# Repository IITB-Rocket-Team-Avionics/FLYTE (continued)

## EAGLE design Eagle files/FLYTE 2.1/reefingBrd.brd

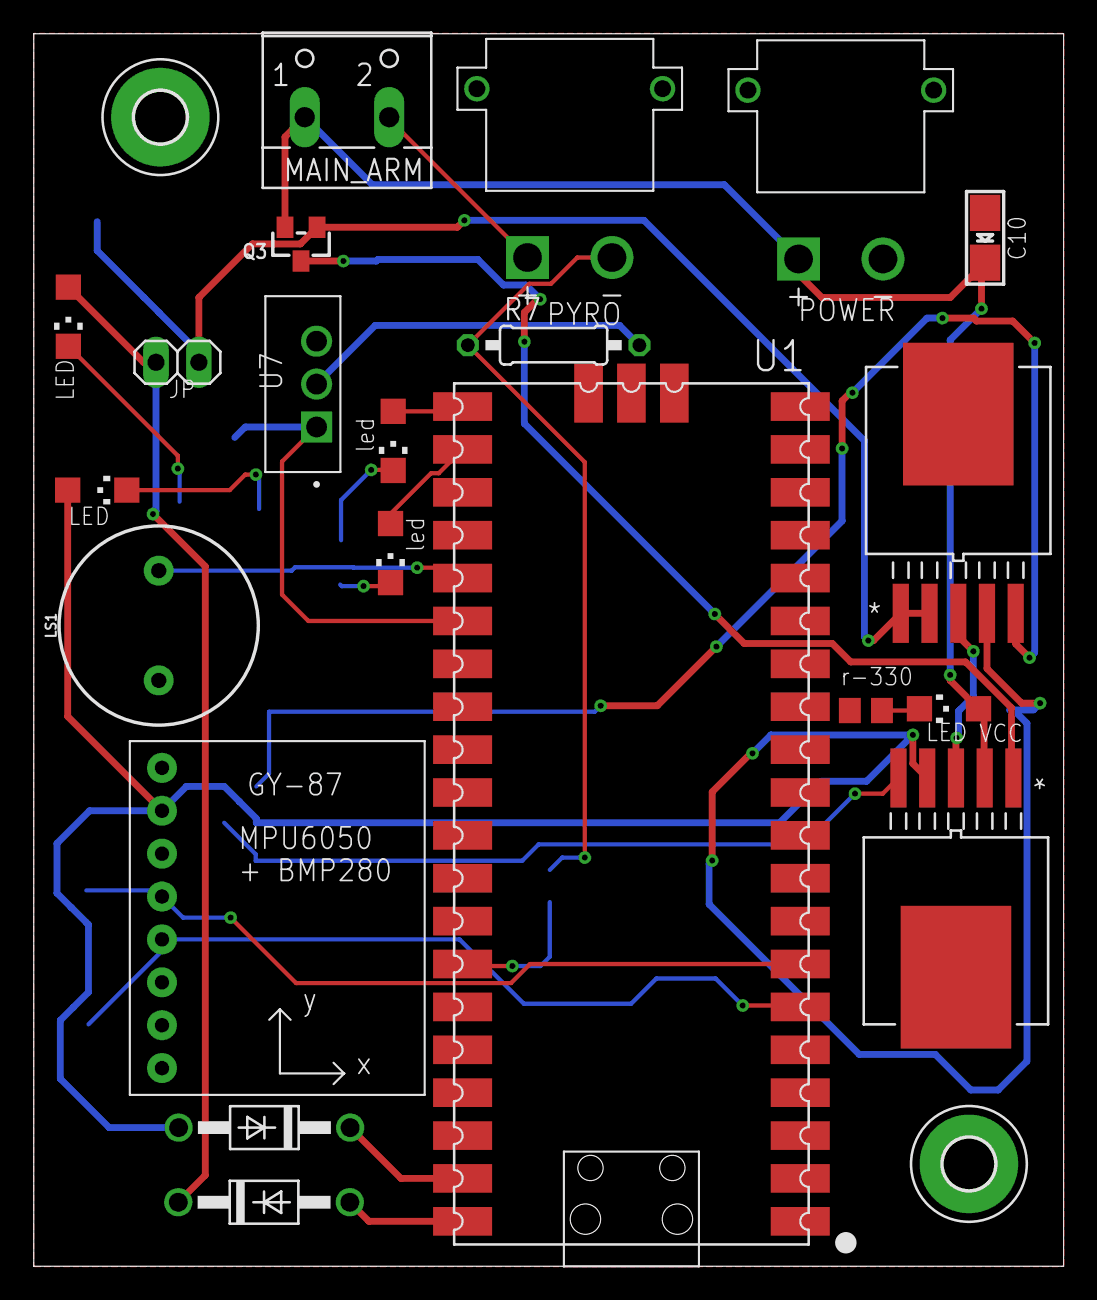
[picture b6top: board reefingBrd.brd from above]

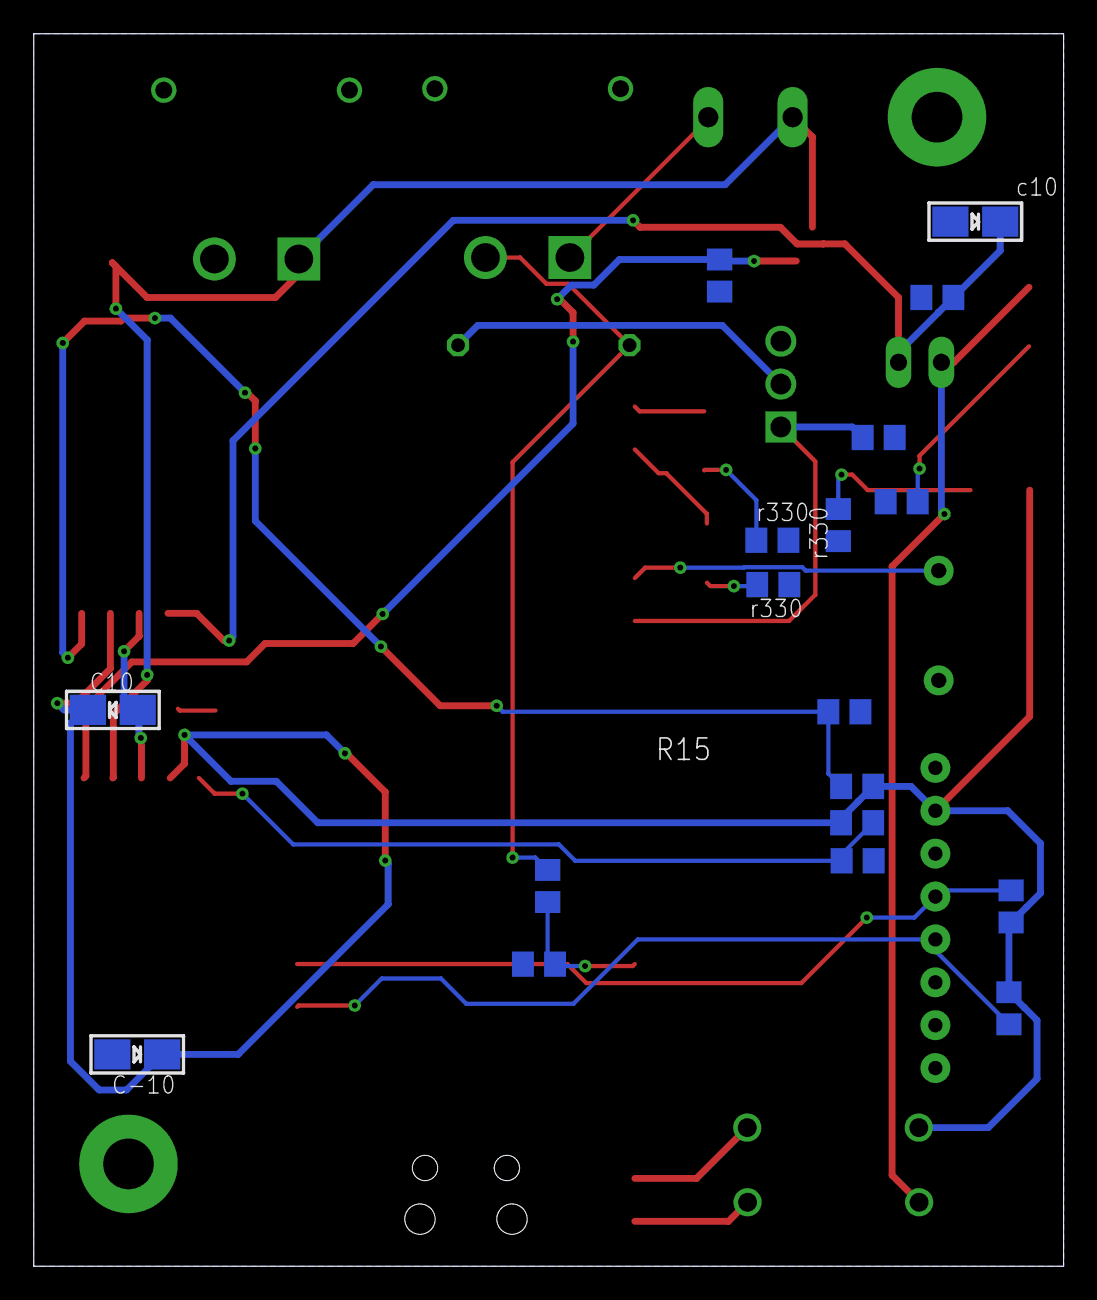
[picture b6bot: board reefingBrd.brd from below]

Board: 2 copper layers, 61.0 x 73.0 mm, 41 parts (18 on the bottom side), 25 nets.

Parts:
C6, C11: 10uF; EIA3216-18/A-W
C7, C12: 10 uF; EIA3216-18/A-W
D1, D3: 1N4004; DO41-10
H1, H2: MOUNT-PAD-ROUND3.0; 3,0-PAD
JP1: 1X02
LED1, LED2, LED3, LED4, LED5: CHIPLED_1206
LS1: BUZZER-PTH; BUZZER-12MM
MAIN_ARM: W237-102
POWER: XT30PW-M; AMASS_XT30PW-M
PYRO: XT30PW-M; AMASS_XT30PW-M
Q3: SOT23-WIDE
R1, R2, R22, R24: 4.7K ohm; R0805
R5, R8: 100K; R0805
R6: 4.7K; R0805
R7: 10 ohm; 0207/10
R9, R10, R11, R12, R13: 330 ohm; R0805
R14, R20: 100K ohm; R0805
R15, R21: 165K ohm; R0805
U1: RASPBERRY_PICOSMD; PICO-PKG-SMD
U2: GY-521MPU6050; GY-521
U3, U4: MIC29302WU-TR; TO-263-5_MCH
U7: IRF540NPBF; TO254P1054X469X1930-3

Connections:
3V3: C7.+, C12.+, D1.A, LED2.A, R1.1, R2.1, R15.1, R21.1, U2.3V3, U3.4, U4.4
BUZZER: LS1.+, U1.P$25
GND: C6.-, C7.-, C11.-, C12.-, H1.B3,0, H2.B3,0, LS1.-, POWER.N, R6.1, R8.1, R9.1, R10.1, R11.1, R12.1, R13.1, R14.2, R20.2, R22.1, R24.1, U1.P$3, U1.P$8, U1.P$13, U1.P$18, U1.P$23, U1.P$28, U1.P$33, U1.P$38, U2.GND, U3.3, U3.6, U4.3, U4.6, U7.3
LED1: LED4.A, U1.P$22
LED2: LED5.A, U1.P$21
MAIN: R6.2, U1.P$26, U7.1
unnamed: D1.C, U1.P$39
unnamed: D3.A, U1.P$40
unnamed: R20.1, R21.2, U4.5
unnamed: PYRO.N, R5.2, R7.1
unnamed: R7.2, U7.2
unnamed: MAIN_ARM.2, PYRO.P
unnamed: R14.1, R15.2, U3.5
unnamed: LED1.C, R9.2
unnamed: LED2.C, R10.2
unnamed: LED3.C, R11.2
unnamed: LED4.C, R12.2
unnamed: LED5.C, R13.2
SCL0: R2.2, U1.P$7, U2.SCL
SDA0: R1.2, U1.P$6, U2.SDA
SENSE_MAIN: R5.1, R8.2, U1.P$34
VBUS: D3.C, JP1.2, LED3.A
VBUS_REG: C6.+, JP1.1, Q3.1, R24.2, U3.1, U3.2
VCC: C11.+, LED1.A, MAIN_ARM.1, POWER.P, Q3.2, U4.2
VCC_EN: Q3.3, R22.2, U4.1

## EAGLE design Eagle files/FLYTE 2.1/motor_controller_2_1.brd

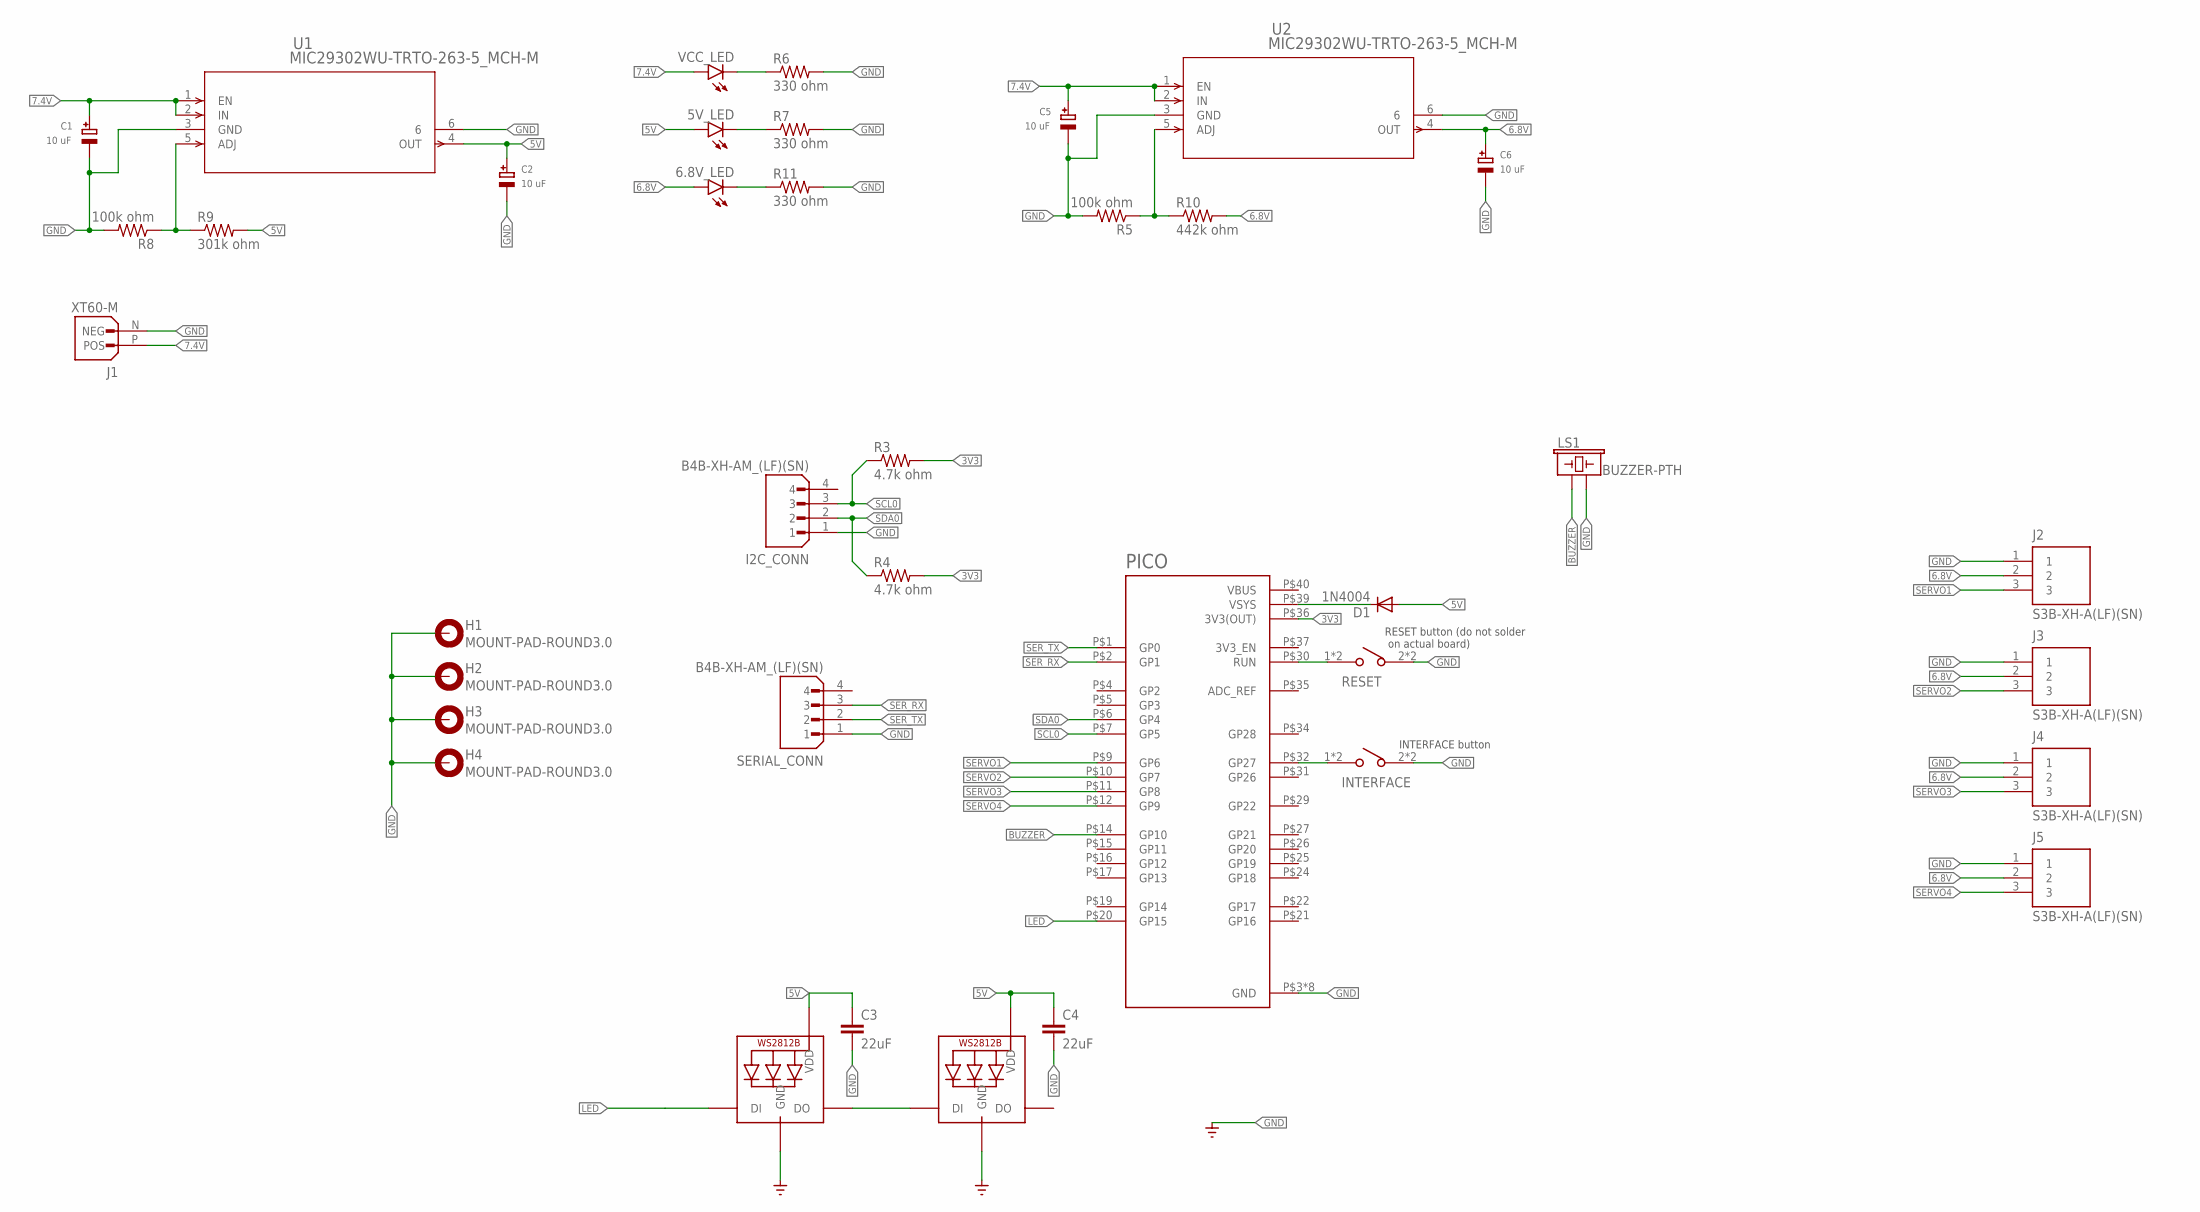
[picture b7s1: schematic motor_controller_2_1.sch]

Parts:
5V_LED, 6.8V_LED: LEDCHIPLED_1206; CHIPLED_1206
C1, C2, C5, C6: 10 uF; EIA3216-18/A-W
C3, C4: 22uF; 0805
D1: 1N4004; DO41-10
H1, H2, H3, H4: MOUNT-PAD-ROUND3.0; 3,0-PAD
I2C_CONN: B4B-XH-AM_(LF)(SN); JST_B4B-XH-AM_(LF)(SN)
INTERFACE: TS04-66-95-BK-100-SMT; SW_TS04-66-95-BK-100-SMT
J1: XT60-M; AMASS_XT60-M
J2, J3, J4, J5: S3B-XH-A(LF)(SN); JST_S3B-XH-A(LF)(SN)
LED1, LED2: WS2812B3535; LED3535
LS1: BUZZER-PTH; BUZZER-12MM
PICO: RASPBERRY_PICO-NO_DEBUG; PICO-PKG-NO_DEBUG
R3, R4: 4.7k ohm; R0805
R5, R8: 100k ohm; R0805
R6, R7, R11: 330 ohm; R0805
R9: 301k ohm; R0805
R10: 442k ohm; R0805
RESET: TS04-66-95-BK-100-SMT; SW_TS04-66-95-BK-100-SMT
SERIAL_CONN: B4B-XH-AM_(LF)(SN); JST_B4B-XH-AM_(LF)(SN)
U1, U2: MIC29302WU-TRTO-263-5_MCH-M; TO-263-5_MCH-M
VCC_LED: LEDCHIPLED_1206; CHIPLED_1206

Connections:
3V3: PICO.P$36 (3V3(OUT)), R3.2, R4.2
5V: 5V_LED.A, C2.+, C3.1, C4.1, D1.A, LED1.2 (VDD), LED2.2 (VDD), R9.2, U1.4 (OUT)
6.8V: 6.8V_LED.A, C6.+, J2.2, J3.2, J4.2, J5.2, R10.2, U2.4 (OUT)
7.4V: C1.+, C5.+, J1.P (POS), U1.1 (EN), U1.2 (IN), U2.1 (EN), U2.2 (IN), VCC_LED.A
BUZZER: LS1.+ (1), PICO.P$14 (GP10)
GND: C1.-, C2.-, C3.2, C4.2, C5.-, C6.-, H1.B3,0, H2.B3,0, H3.B3,0, H4.B3,0, I2C_CONN.1, INTERFACE.2 (4), INTERFACE.4, J1.N (NEG), J2.1, J3.1, J4.1, J5.1, LED1.4 (GND), LED2.4 (GND), LS1.- (2), PICO.P$3 (GND), PICO.P$8 (GND), PICO.P$13 (GND), PICO.P$18 (GND), PICO.P$23 (GND), PICO.P$28 (GND), PICO.P$33 (GND), PICO.P$38 (GND), R5.2, R6.2, R7.2, R8.2, R11.2, RESET.2 (4), RESET.4, SERIAL_CONN.1, U1.3 (GND), U1.6, U2.3 (GND), U2.6
LED: LED1.1 (DI), PICO.P$20 (GP15)
unnamed: D1.C, PICO.P$39 (VSYS)
unnamed: PICO.P$30 (RUN), RESET.1 (2), RESET.3 (2)
unnamed: INTERFACE.1 (2), INTERFACE.3 (2), PICO.P$32 (GP27)
unnamed: R5.1, R10.1, U2.5 (ADJ)
unnamed: LED1.3 (DO), LED2.1 (DI)
unnamed: 6.8V_LED.C, R11.1
unnamed: R6.1, VCC_LED.C
unnamed: 5V_LED.C, R7.1
unnamed: R8.1, R9.1, U1.5 (ADJ)
SCL0: I2C_CONN.3, PICO.P$7 (GP5), R3.1
SDA0: I2C_CONN.2, PICO.P$6 (GP4), R4.1
SERVO1: J2.3, PICO.P$9 (GP6)
SERVO2: J3.3, PICO.P$10 (GP7)
SERVO3: J4.3, PICO.P$11 (GP8)
SERVO4: J5.3, PICO.P$12 (GP9)
SER_RX: PICO.P$2 (GP1), SERIAL_CONN.3
SER_TX: PICO.P$1 (GP0), SERIAL_CONN.2
VBUS: PICO.P$40 (VBUS)

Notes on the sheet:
RESET button (do not solder on actual board)
INTERFACE button

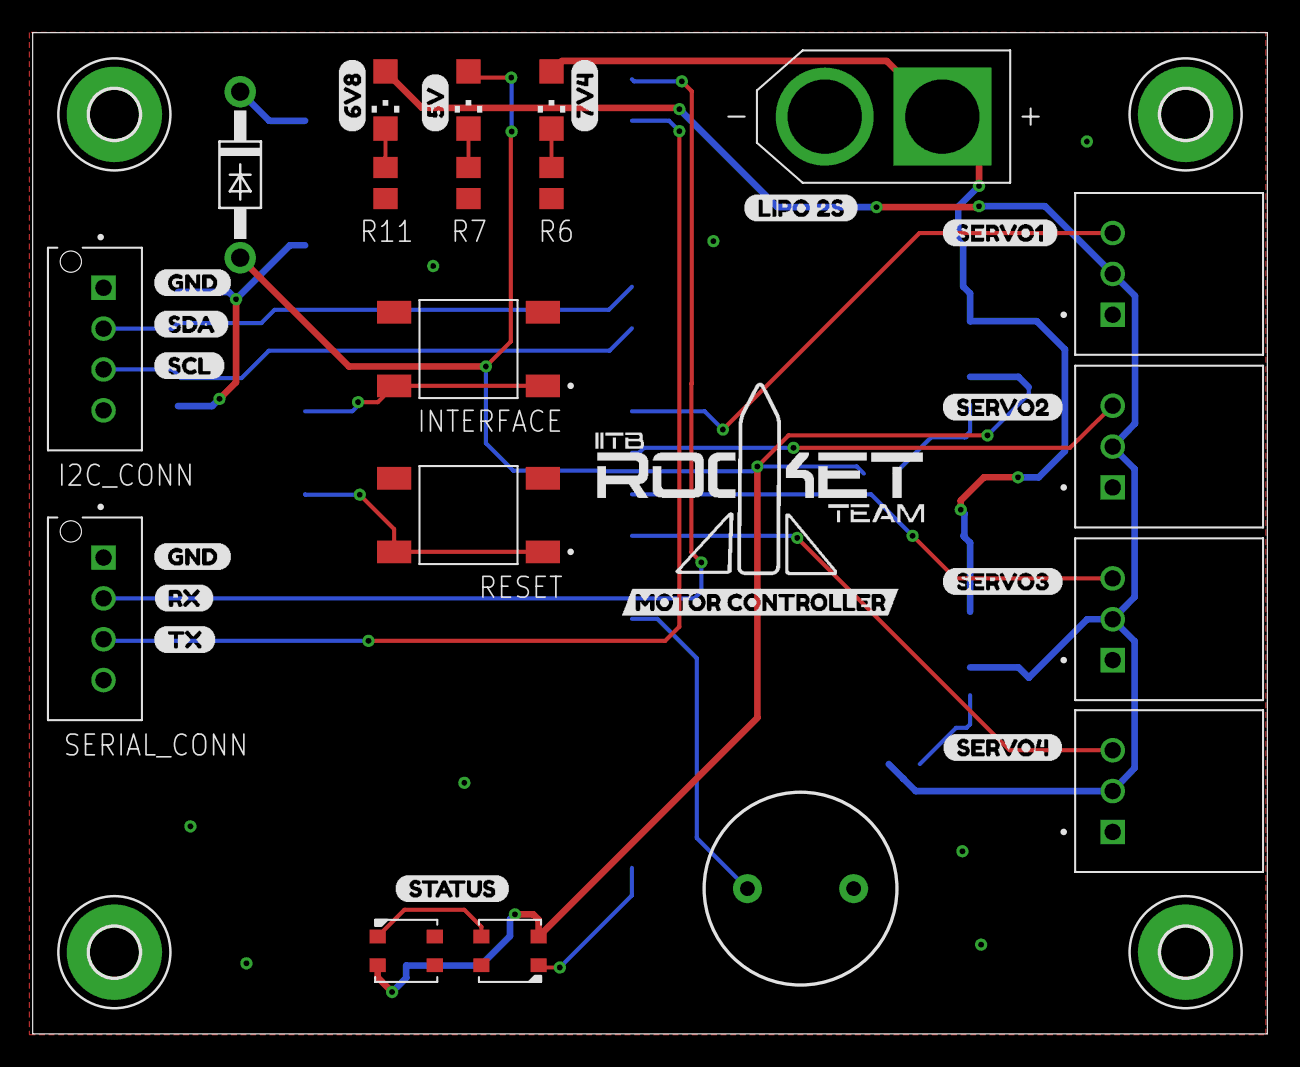
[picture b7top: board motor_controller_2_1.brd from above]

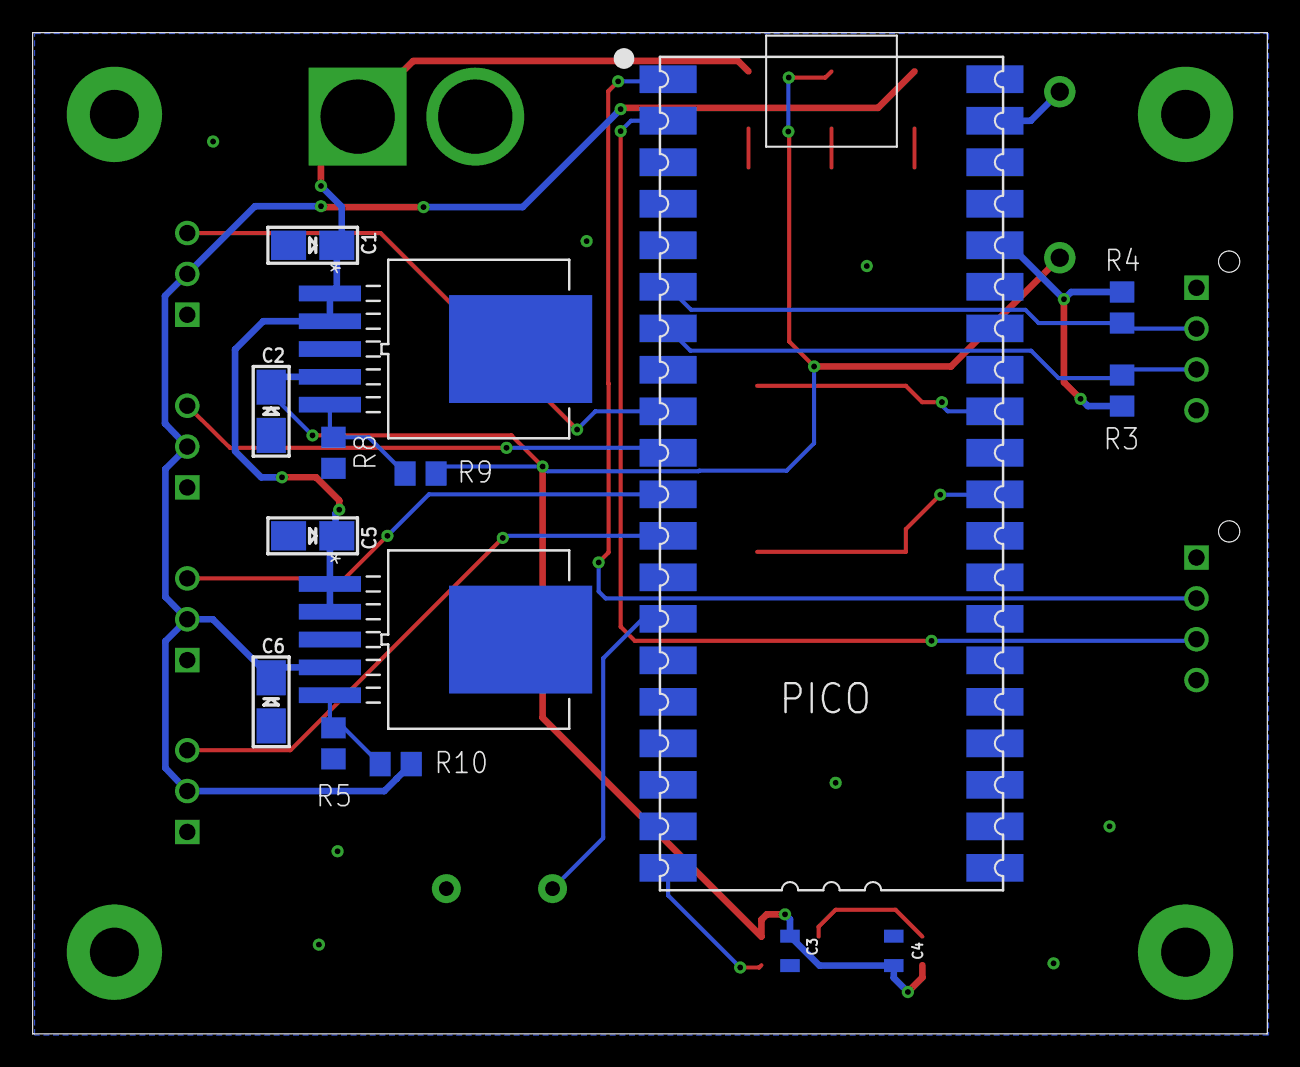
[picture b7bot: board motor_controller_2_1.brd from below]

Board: 2 copper layers, 75.6 x 61.3 mm, 54 parts (15 on the bottom side), 24 nets.

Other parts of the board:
U$1: SERVO10
U$2: SERVO20
U$3: SERVO30
U$4: SERVO40
U$5: SDA0
U$6: SCL0
U$7, U$8: GND0
U$9: RX0
U$10: TX0
U$11: LIPO_2S0
U$12: 5V0
U$13: 7V40
U$14: 6V80
U$15: STATUS0
U$16: MOTOR_CONTROLLER0

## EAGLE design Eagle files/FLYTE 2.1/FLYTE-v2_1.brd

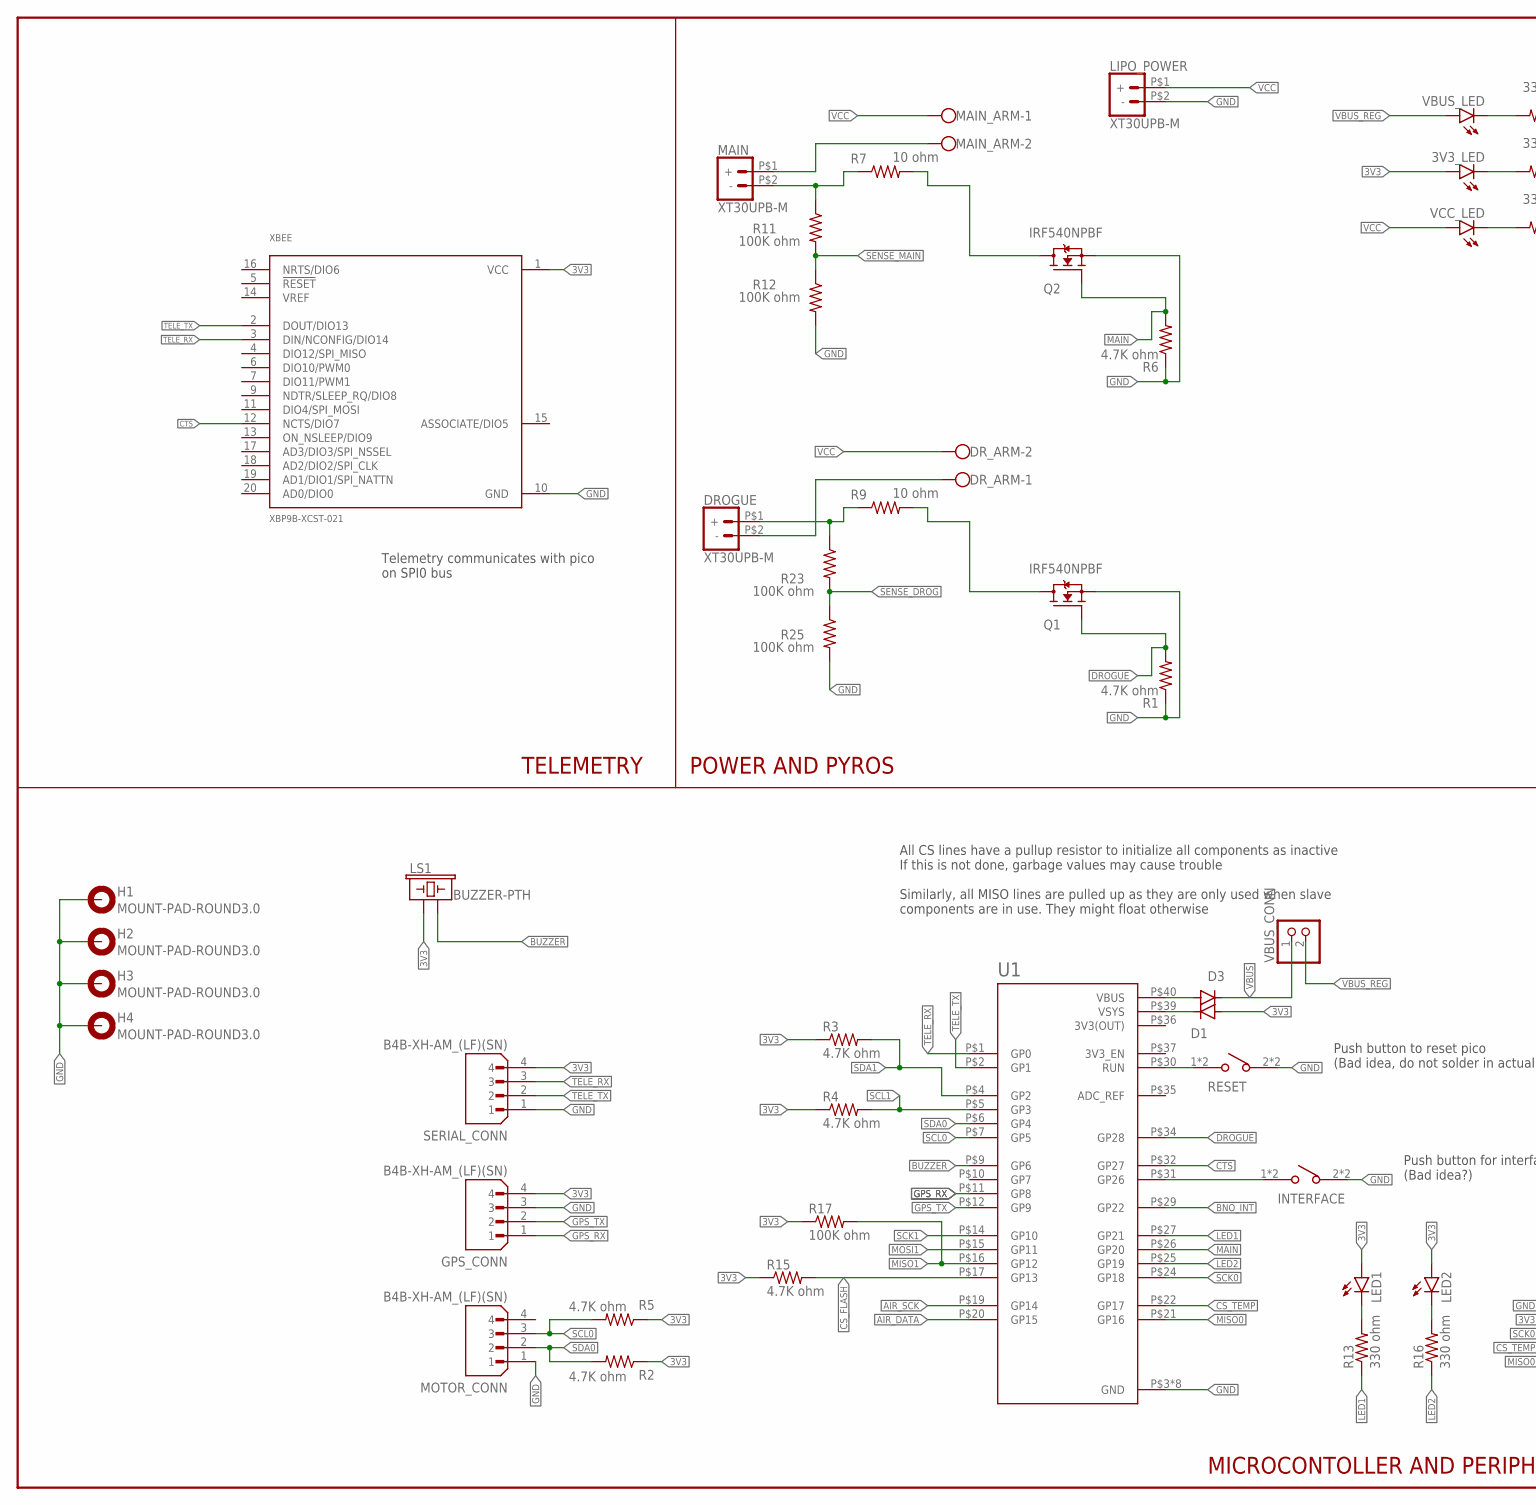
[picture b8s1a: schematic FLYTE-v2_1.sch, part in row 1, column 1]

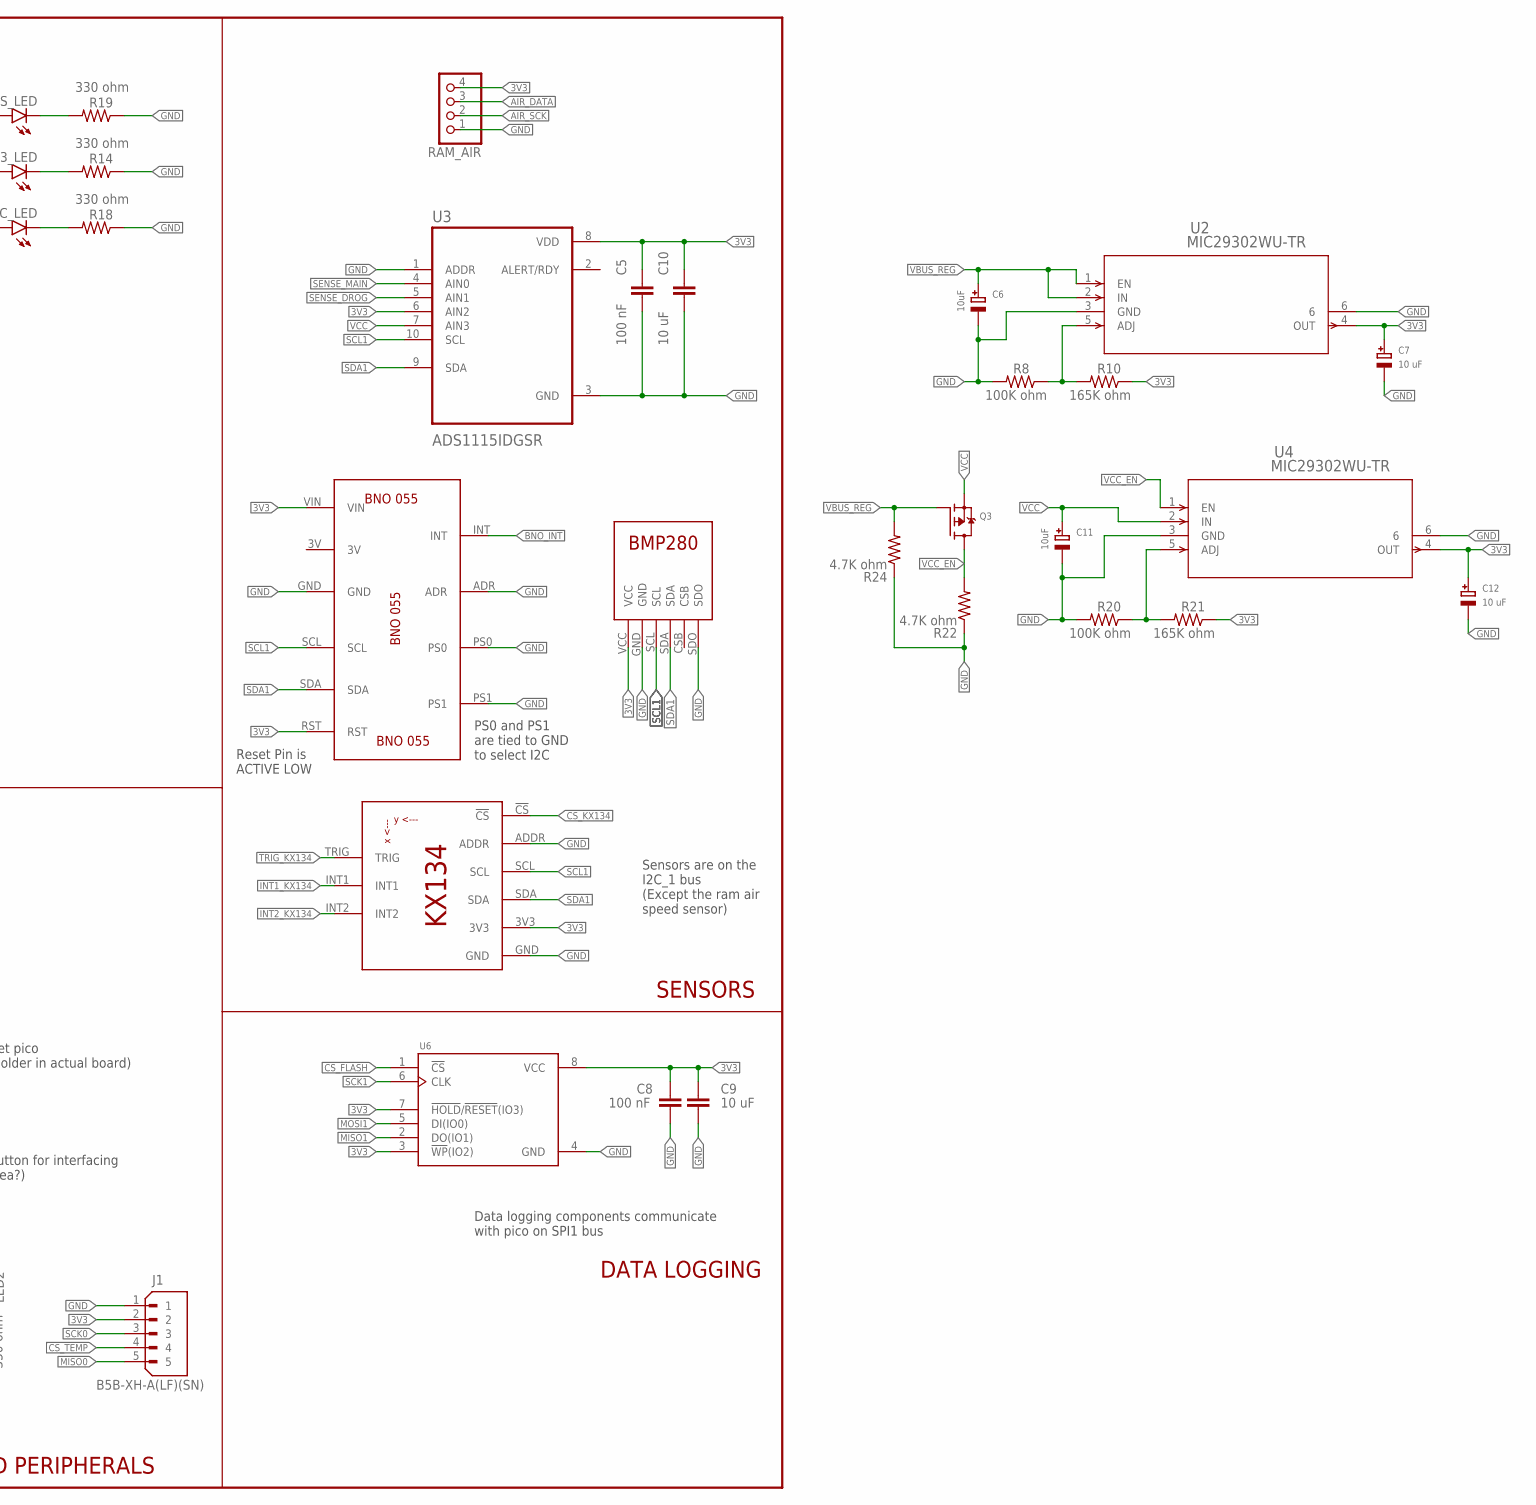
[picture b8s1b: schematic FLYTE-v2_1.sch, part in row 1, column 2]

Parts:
3V3_LED: LEDCHIPLED_1206; CHIPLED_1206
C5, C8: 100 nF; 0805
C6, C11: 10uF; EIA3216-18/A-W
C7, C12: 10 uF; EIA3216-18/A-W
C9, C10: 10 uF; 0805
D1, D3: 1N4004; DO41-10
DROGUE: XT30UPB-M
DR_ARM: W237-102
GPS_CONN: B4B-XH-AM_(LF)(SN); JST_B4B-XH-AM_(LF)(SN)
H1, H2, H3, H4: MOUNT-PAD-ROUND3.0; 3,0-PAD
INTERFACE: TS04-66-95-BK-100-SMT; SW_TS04-66-95-BK-100-SMT
J1: B5B-XH-A(LF)(SN); JST_B5B-XH-A(LF)(SN)
LED1, LED2: LEDCHIPLED_1206; CHIPLED_1206
LIPO_POWER: XT30UPB-M
LS1: BUZZER-PTH; BUZZER-12MM
MAIN: XT30UPB-M
MAIN_ARM: W237-102
MOTOR_CONN: B4B-XH-AM_(LF)(SN); JST_B4B-XH-AM_(LF)(SN)
Q1, Q2: IRF540NPBF; TO254P1054X469X1930-3
Q3: MOSFET-PWIDE; SOT23-WIDE
R1, R2, R3, R4, R5, R6, R15, R22, R24: 4.7K ohm; R0805
R7, R9: 10 ohm; 0207/10
R8, R11, R12, R17, R20, R23, R25: 100K ohm; R0805
R10, R21: 165K ohm; R0805
R13, R14, R16, R18, R19: 330 ohm; R0805
RAM_AIR: PINHD-1X4; 1X04
RESET: TS04-66-95-BK-100-SMT; SW_TS04-66-95-BK-100-SMT
SERIAL_CONN: B4B-XH-AM_(LF)(SN); JST_B4B-XH-AM_(LF)(SN)
U1: RASPBERRY_PICO-NO_DEBUG; PICO-PKG-NO_DEBUG
U2, U4: MIC29302WU-TR; TO-263-5_MCH
U3: ADS1115IDGSR; SOP50P490X110-10N
U6: W25Q32JVSSIQ; SOIC127P790X216-8N
U$1: BMP280
U$2: KX134-BREAKOUT
U$4: BNO055
VBUS_CONN: PINHD-1X2; 1X02
VBUS_LED: LEDCHIPLED_1206; CHIPLED_1206
VCC_LED: LEDCHIPLED_1206; CHIPLED_1206
XBEE: XBP9B-XCST-021; DIP2200W51P200L3294H279Q20P

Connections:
3V3: 3V3_LED.A, C5.1, C7.+, C8.2, C9.2, C10.1, C12.+, D1.A, GPS_CONN.4, J1.2, LED1.A, LED2.A, LS1.+ (1), R2.1, R3.1, R4.1, R5.1, R10.1, R15.1, R17.1, R21.1, RAM_AIR.4, SERIAL_CONN.4, U2.4 (OUT), U3.6 (AIN2), U3.8 (VDD), U4.4 (OUT), U6.3 (!WP!(IO2)), U6.7 (!HOLD!/!RESET!(IO3)), U6.8 (VCC), U$1.VCC, U$2.3V3, U$4.RST, U$4.VIN, XBEE.1 (VCC)
3V3(OUT): U1.P$36 (3V3(OUT))
AIR_DATA: RAM_AIR.3, U1.P$20 (GP15)
AIR_SCK: RAM_AIR.2, U1.P$19 (GP14)
BNO_INT: U1.P$29 (GP22), U$4.INT
BUZZER: LS1.- (2), U1.P$9 (GP6)
CS_FLASH: R15.2, U1.P$17 (GP13), U6.1 (!CS)
CS_KX134: U$2.!CS
CS_TEMP: J1.4, U1.P$22 (GP17)
CTS: U1.P$32 (GP27), XBEE.12 (NCTS/DIO7)
DROGUE: Q1.1 (G), R1.2, U1.P$34 (GP28)
GND: C5.2, C6.-, C7.-, C8.1, C9.1, C10.2, C11.-, C12.-, GPS_CONN.3, H1.B3,0, H2.B3,0, H3.B3,0, H4.B3,0, INTERFACE.2 (4), INTERFACE.4, J1.1, LIPO_POWER.P$2 (-), MOTOR_CONN.1, Q1.3 (S), Q2.3 (S), R1.1, R6.1, R8.2, R12.2, R14.1, R18.1, R19.1, R20.2, R22.1, R24.1, R25.2, RAM_AIR.1, RESET.2 (4), RESET.4, SERIAL_CONN.1, U1.P$3 (GND), U1.P$8 (GND), U1.P$13 (GND), U1.P$18 (GND), U1.P$23 (GND), U1.P$28 (GND), U1.P$33 (GND), U1.P$38 (GND), U2.3 (GND), U2.6, U3.1 (ADDR), U3.3 (GND), U4.3 (GND), U4.6, U6.4 (GND), U$1.GND, U$1.SDO, U$2.ADDR, U$2.GND, U$4.ADR, U$4.GND, U$4.PS0, U$4.PS1, XBEE.10 (GND)
GPS_RX: GPS_CONN.1, U1.P$11 (GP8)
GPS_TX: GPS_CONN.2, U1.P$12 (GP9)
INT1_KX134: U$2.INT1
INT2_KX134: U$2.INT2
LED1: R13.1, U1.P$27 (GP21)
LED2: R16.1, U1.P$25 (GP19)
MAIN: Q2.1 (G), R6.2, U1.P$26 (GP20)
MISO0: J1.5, U1.P$21 (GP16)
MISO1: R17.2, U1.P$16 (GP12), U6.2 (DO(IO1))
MOSI1: U1.P$15 (GP11), U6.5 (DI(IO0))
unnamed: D1.C, U1.P$39 (VSYS)
unnamed: DROGUE.P$2 (-), DR_ARM.1
unnamed: INTERFACE.1 (2), INTERFACE.3 (2), U1.P$31 (GP26)
unnamed: MAIN.P$2 (-), R7.1, R11.1
unnamed: R20.1, R21.2, U4.5 (ADJ)
unnamed: MAIN.P$1 (+), MAIN_ARM.2
unnamed: DROGUE.P$1 (+), R9.1, R23.1
unnamed: RESET.1 (2), RESET.3 (2), U1.P$30 (RUN)
unnamed: R8.1, R10.2, U2.5 (ADJ)
unnamed: Q2.2 (D), R7.2
unnamed: Q1.2 (D), R9.2
unnamed: R19.2, VBUS_LED.C
unnamed: LED1.C, R13.2
unnamed: LED2.C, R16.2
unnamed: 3V3_LED.C, R14.2
unnamed: D3.A, U1.P$40 (VBUS)
unnamed: R18.2, VCC_LED.C
SCK0: J1.3, U1.P$24 (GP18)
SCK1: U1.P$14 (GP10), U6.6 (CLK)
SCL0: MOTOR_CONN.3, R5.2, U1.P$7 (GP5)
SCL1: R4.2, U1.P$5 (GP3), U3.10 (SCL), U$1.SCL, U$2.SCL, U$4.SCL
SDA0: MOTOR_CONN.2, R2.2, U1.P$6 (GP4)
SDA1: R3.2, U1.P$4 (GP2), U3.9 (SDA), U$1.SDA, U$2.SDA, U$4.SDA
SENSE_DROG: R23.2, R25.1, U3.5 (AIN1)
SENSE_MAIN: R11.2, R12.1, U3.4 (AIN0)
TELE_RX: SERIAL_CONN.3, U1.P$1 (GP0), XBEE.3 (DIN/NCONFIG/DIO14)
TELE_TX: SERIAL_CONN.2, U1.P$2 (GP1), XBEE.2 (DOUT/DIO13)
TRIG_KX134: U$2.TRIG
VBUS: D3.C, VBUS_CONN.1
VBUS_REG: C6.+, Q3.1 (G), R24.2, U2.1 (EN), U2.2 (IN), VBUS_CONN.2, VBUS_LED.A
VCC: C11.+, DR_ARM.2, LIPO_POWER.P$1 (+), MAIN_ARM.1, Q3.2 (S), U3.7 (AIN3), U4.2 (IN), VCC_LED.A
VCC_EN: Q3.3 (D), R22.2, U4.1 (EN)

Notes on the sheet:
Telemetry communicates with pico on SPI0 bus
Data logging components communicate with pico on SPI1 bus
All CS lines have a pullup resistor to initialize all components as inactive If this is not done, garbage values may cause trouble Similarly, all MISO lines are pulled up as they are only used when slave components are in use. They might float otherwise
Push button to reset pico (Bad idea, do not solder in actual board)
Push button for interfacing (Bad idea?)
Sensors are on the I2C_1 bus (Except the ram air speed sensor)
MICROCONTOLLER AND PERIPHERALS
TELEMETRY
POWER AND PYROS
SENSORS
DATA LOGGING
Reset Pin is ACTIVE LOW
PS0 and PS1 are tied to GND to select I2C

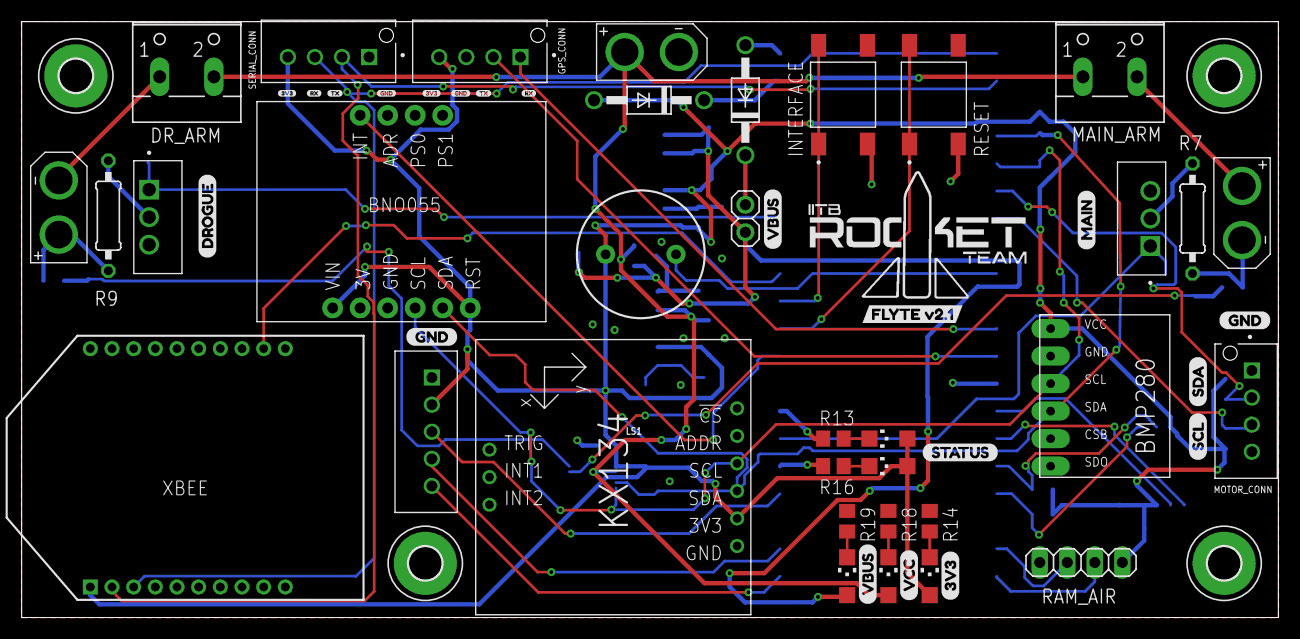
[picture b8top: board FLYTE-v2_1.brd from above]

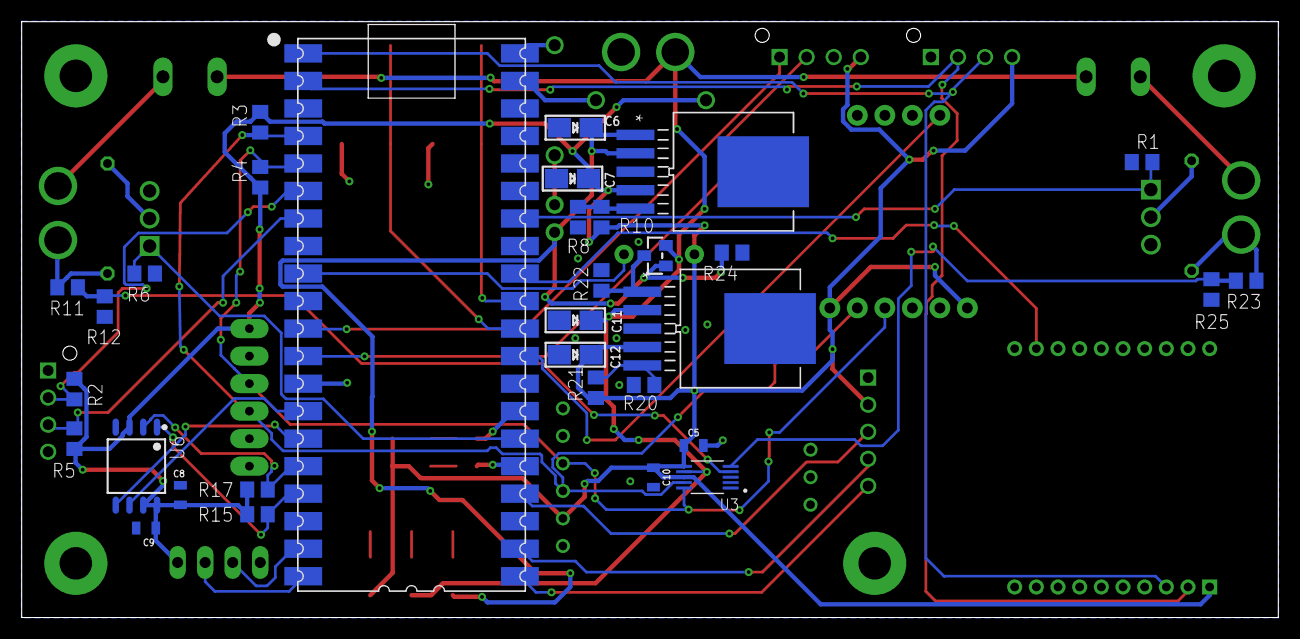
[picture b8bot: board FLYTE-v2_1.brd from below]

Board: 2 copper layers, 116.0 x 55.0 mm, 90 parts (32 on the bottom side), 49 nets.

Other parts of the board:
U$3, U$15, U$18, U$21: GND0
U$5, U$19, U$20: 3V30
U$9: STATUS0
U$10: VCC0
U$11, U$26: VBUS0
U$12: MAIN0
U$13: DROGUE0
U$16: SCL0
U$17: SDA0
U$22, U$23: RX0
U$24, U$25: TX0
U$27: FLYTE_V2#10

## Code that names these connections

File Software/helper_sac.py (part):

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        self.bmp, self.mpu, self.sd, self.sx, self.gps, self.flash = None, None, None, None, None, None
        self.led = Pin(25, Pin.OUT)
        self.led.value(0)
        self.buzzer = PWM(Pin(6))
        self.buzzer.freq(2000)
        self.buzzer.duty_u16(0)
        self.lock = _thread.allocate_lock()
        self.run_state = 0    # 0: All threads off
                              # 1: Signal the threads to start
                              # 2: Threads are running
        self.prog = Pin(14, Pin.IN, Pin.PULL_DOWN)
        self.except_occr = False
        self.data_array = bytearray()
        self.data_fast = bytes(32)
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        self.shutdown = False
        self.send_calib = False
        self.calib_data = bytes(20)
        self.drogue = Pin(15, Pin.OUT)
        self.main = Pin(20, Pin.OUT)
        self.drogue.value(0)
        self.main.value(0)
#         self.tim = Timer()
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                    miso=Pin(12))
        
        self.SD_CS = Pin(13) # Chip Select for SD Card
        self.flash_CS = Pin(9)
        
        #uart bus
        self.uart = UART(0, 9600, rx = Pin(1), tx = Pin(0), timeout=1000, timeout_char=1000) # decide on timeouts
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
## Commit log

2023-05-07 Init libraries
2023-05-07 Add 3D model files
2023-05-10 Modify pyro and power section
2023-05-13 Finish chematic except gps
2023-05-13 Finish v1 schematic
2023-05-14 Finish layout
2023-05-14 Finish layout with GPS
2023-05-14 move resistors, remove 1 screw sw
2023-05-16 Finish wiring and top layout
2023-05-17 Finish board
2023-05-17 Minor fixes
2023-05-19 Add ground station
2023-05-19 Add ground vias
2023-05-21 Finish ground station
2023-05-24 Minor changes
2023-06-07 Finish fast core code
2023-06-09 update fsm and clean up
2023-06-09 complete fast core
2023-06-12 Add SD mount protection and debug slow core encoding
2023-06-14 Make improvements to code
2023-06-20 Modifications for final launch
2023-06-20 Change timings
2023-06-21 Add pyro test file and tweak helper
2023-06-21 Remove prog switch
2023-12-06 Cleanup resistors, add ADC
2023-12-09 a few libraries added and BNO055 lbr changed
2023-12-09 a few more small changes
2023-12-09 updated adxl and bno libs
2023-12-10 bno added
2023-12-11 Add JST, MOSFET, and high g accel
2023-12-19 sensor data from car rides
2023-12-20 Improve pyros
2023-12-21 ins/gnss coupling analyzer added
2023-12-25 added gnss aided acceleromter bias estimation
2023-12-26 improved gnss aided accelerometer bias estimation
2024-01-01 cleanup
2024-01-02 Cleanup main board and add motor controller
2024-01-04 Start layout
2024-01-04 made all functions async
2024-01-09 routing done
2024-01-10 new layout
2024-01-17 Resolve clearance issue:
2024-01-17 errors destroyed
2024-01-17 uart xbee
2024-01-18 layout done. drc left to clear
2024-01-18 updated layout
2024-01-18 layout done
2024-01-18 Start motor conroller layout
2024-01-19 Finish layout for v2
2024-01-19 Finish schematic for motor controller
2024-01-19 Thoda aur
2024-01-19 Aur thoda
2024-01-19 Finish flyte v2
2024-01-20 mc done
2024-01-20 Finish motor controller
2024-01-21 added state machine (tested launch 3 ok)
2024-01-25 Reefing board model
2024-02-15 Add motor controller i2c slave code
2024-02-17 Async code woah
2024-02-18 load
2024-02-28 Add littleFS and cleanup asyncio code
2024-03-12 Created a folder for libraries of payload sensors
2024-03-12 library for UV sensor
2024-03-12 Library for Lux sensor
2024-03-12 library for Temp, pressure, humidity
2024-03-13 Moved the libr_payload folder from eagle to software as it has python libraries
2024-03-13 Created a folder for eagle libs and added readme
2024-03-13 Eagle Library files added for lux and UV sensor
2024-03-22 libs for payload basic
2024-03-22 payload libs added
2024-04-22 Add FLYTE v2.1 files
2024-04-25 motor controller re design
2024-04-26 current code
2024-04-30 Schematics of FC and motor controller
2024-05-01 Schem of fc and mc
2024-05-03 payload added
2024-05-04 payload sch 408 mc board
2024-05-04 payload. yet to be verified
2024-05-04 payload pushed
2024-05-04 Added libs for payload and moved payload under eagle files
2024-05-05 mc 1.0
2024-05-05 mc2.0
2024-05-08 motor controller v2.1
2024-05-08 flyte done
2024-05-09 reefing
2024-05-14 kx134 added in folder kx in software_v2
2024-05-20 new reef
2024-05-30 code update
2024-06-24 agastya
2024-07-26 RP2040 Minimal
2024-08-08 RF Test Board Documentation
2024-09-10 FLYTE 3.0
2024-09-21 3.01
2025-02-02 FLYTE 3.02
2025-02-10 Added the eagle files
2025-02-11 Added the Ground Station Eagle files
2025-02-12 Added the crystel oscillator to the board
2025-02-15 Added USB-C and RESET button and corrections in Crystal Oscillator
2025-02-16 Refined power design with Schottky diode multiplexer and Buck converter
2025-02-17 Finalized power regulation
2025-03-03 Refined power supply design for 5V and added the XT60 M connector
2025-03-05 Added buttons
2025-03-08 revision 1
2025-03-08 Revision 1.01
2025-03-09 Update GND_SATION_PCB_1.02.sch
    NJIIUHHJ IH
2025-03-09 Create USB Type-C Spec R2.0 - August 2019.pdf
    hvf
2025-03-09 Refined the connections for peripherals
2025-03-10 Create si7625dn.pdf
    HI
2025-03-10 gs 1.0 update
2025-03-24 gs updates
2025-03-29 H
    H
2025-05-15 Added the GND_STN.brd file
2025-05-17 Updated the traces
2025-09-28 Added the RP2354 library for eagle
